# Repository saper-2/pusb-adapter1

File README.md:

# PoweredUSB Adapter board
This repo contains design files for PoweredUSB adapter to USB-C (USB 1.1/2.0 mode) or pinheader with additional power connector (barrel jack socket 5,5x2,1(2,5)mm or JST 2.5mm).

In zip file `PoweredUSB-Adapter-PCB-Fab-Files.zip` are packed gerbers for pcb fab house (this is compressed `out` folder).

In schematic (PDF too) you'll find  part numbers.

In folder `Images` you'll find some 3d renders and pcb dimensions.

## Adapter chassis

In `Chassis` folder you'll find a STLs for adapter box, check readme inside for assembly details.

## Stand
I have designed desk stand for those displays, you can find STL to print on 3D printer (FDM) in `Stand` (and some photos).

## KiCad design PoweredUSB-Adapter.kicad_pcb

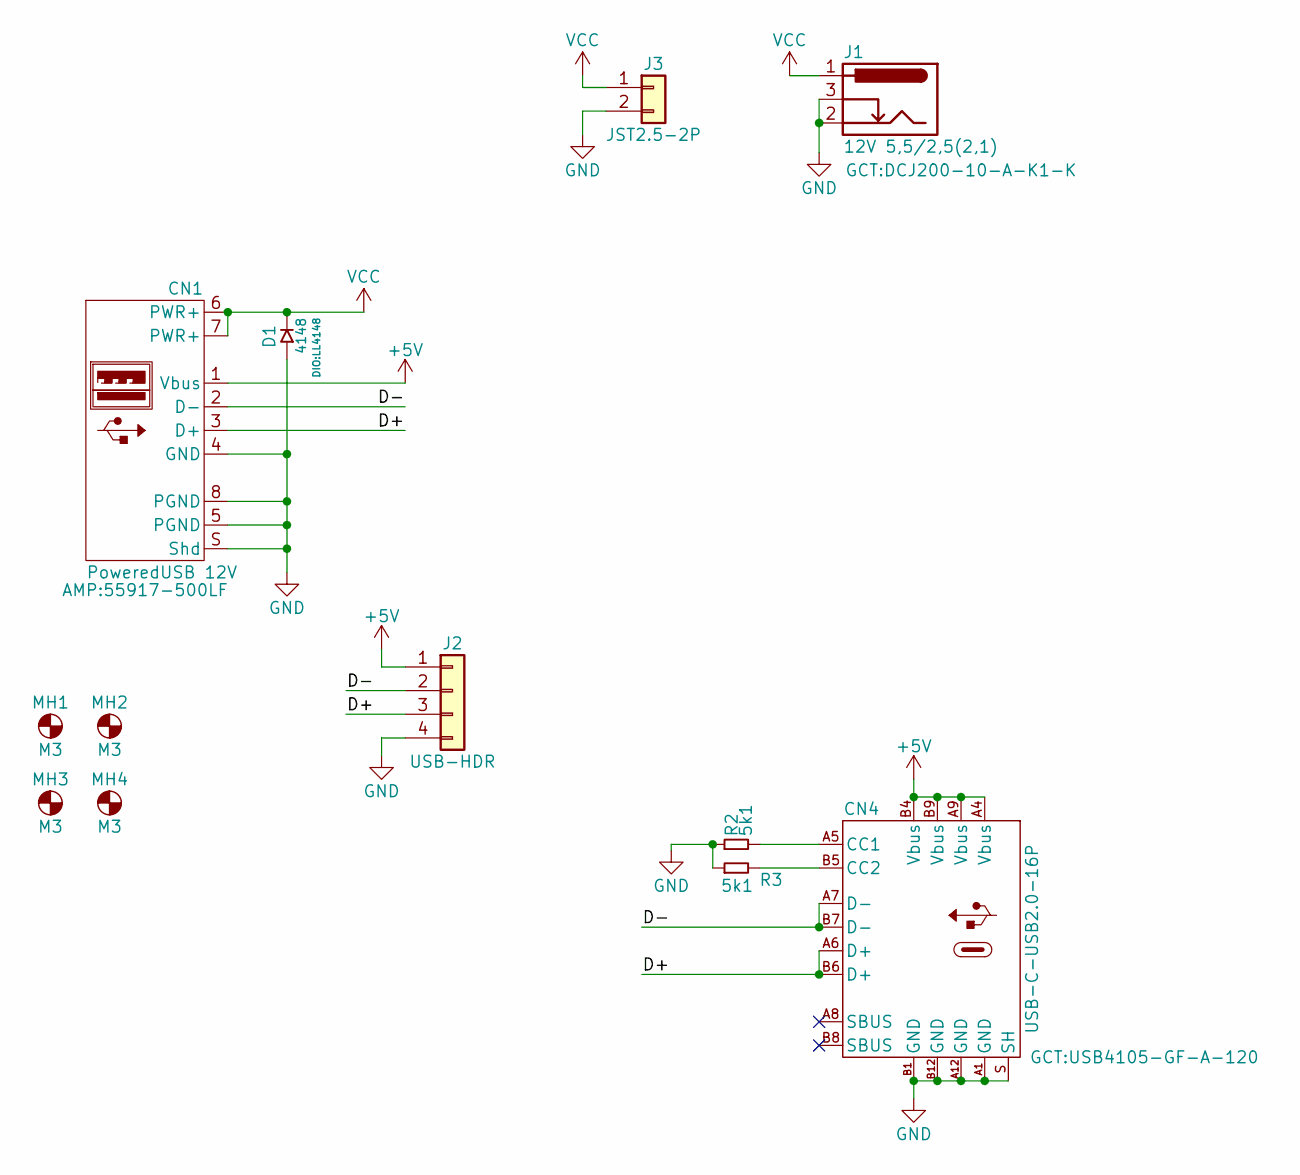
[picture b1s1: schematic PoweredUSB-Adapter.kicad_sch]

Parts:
CN1: PoweredUSB 12V; AMP_55917-500LF
CN4: USB-C-USB2.0-16P; USBC-F-USB2-16P
D1: 4148; D_MiniMELF_HS
J1: 12V 5,5/2,5(2,1); DC_POWER
J2: USB-HDR; HDR1X04_V
J3: JST2.5-2P; WG04S-2.5-02P-V
MH1, MH2, MH3, MH4: M3; MHOLE-3.2MM
R2, R3: 5k1; R_0402_HS2

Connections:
+5V: CN1.1 (Vbus), CN4.A4 (Vbus), CN4.A9 (Vbus), CN4.B4 (Vbus), CN4.B9 (Vbus), J2.1
/D+: CN1.3 (D+), CN4.A6 (D+), CN4.B6 (D+), J2.3
/D-: CN1.2 (D-), CN4.A7 (D-), CN4.B7 (D-), J2.2
GND: CN1.4 (GND), CN1.5 (PGND), CN1.8 (PGND), CN1.S (Shd), CN4.A1 (GND), CN4.A12 (GND), CN4.B1 (GND), CN4.B12 (GND), CN4.S (SH), D1.2 (A), J1.2, J1.3, J2.4, J3.2, R2.1, R3.1
unnamed: CN4.A5 (CC1), R2.2
unnamed: CN4.B5 (CC2), R3.2
VCC: CN1.6 (PWR+), CN1.7 (PWR+), D1.1 (C), J1.1, J3.1

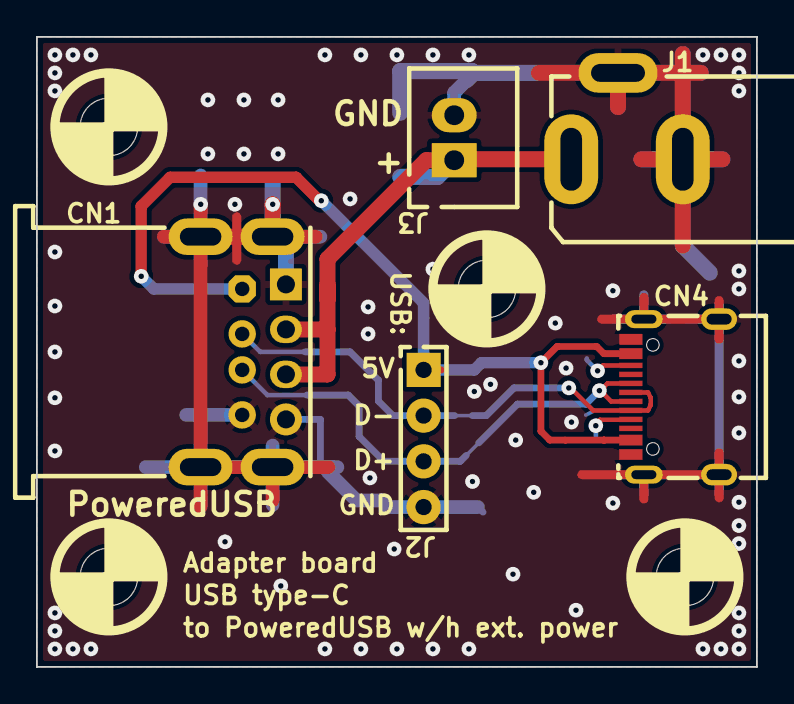
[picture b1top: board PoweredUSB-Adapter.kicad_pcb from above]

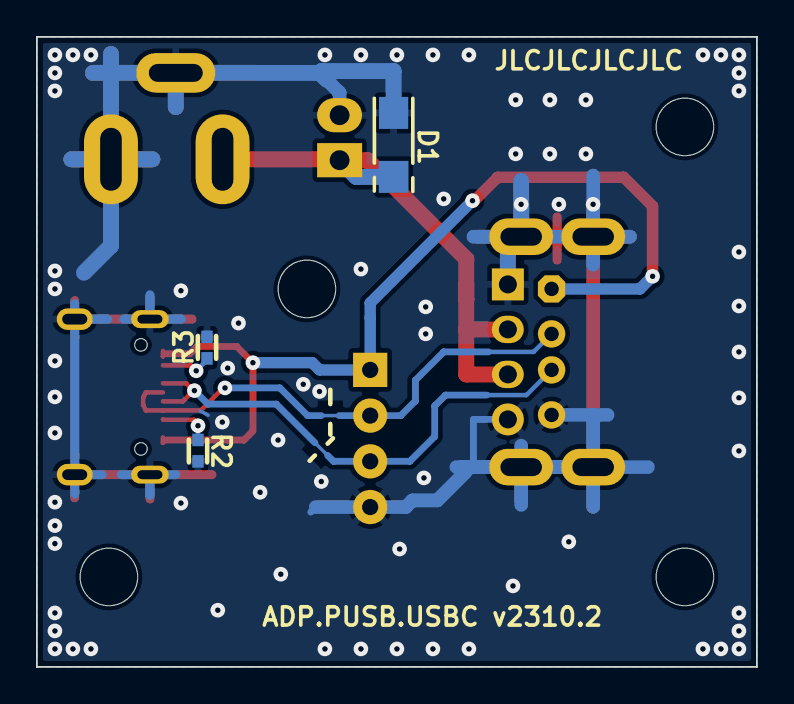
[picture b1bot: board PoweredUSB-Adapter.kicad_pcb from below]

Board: 2 copper layers, 40.0 x 35.0 mm, 12 parts (3 on the bottom side), 7 nets.

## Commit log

2024-01-02 initial release.
